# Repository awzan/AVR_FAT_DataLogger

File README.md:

# AVR_FAT_Data_Logger with DS18B20 temperature sensor

Files in this repository will work only on specific configuration of AVR Atmega32 microcontroller and its peripheries, described in Eagle file PM2016.sch (board scheme file)

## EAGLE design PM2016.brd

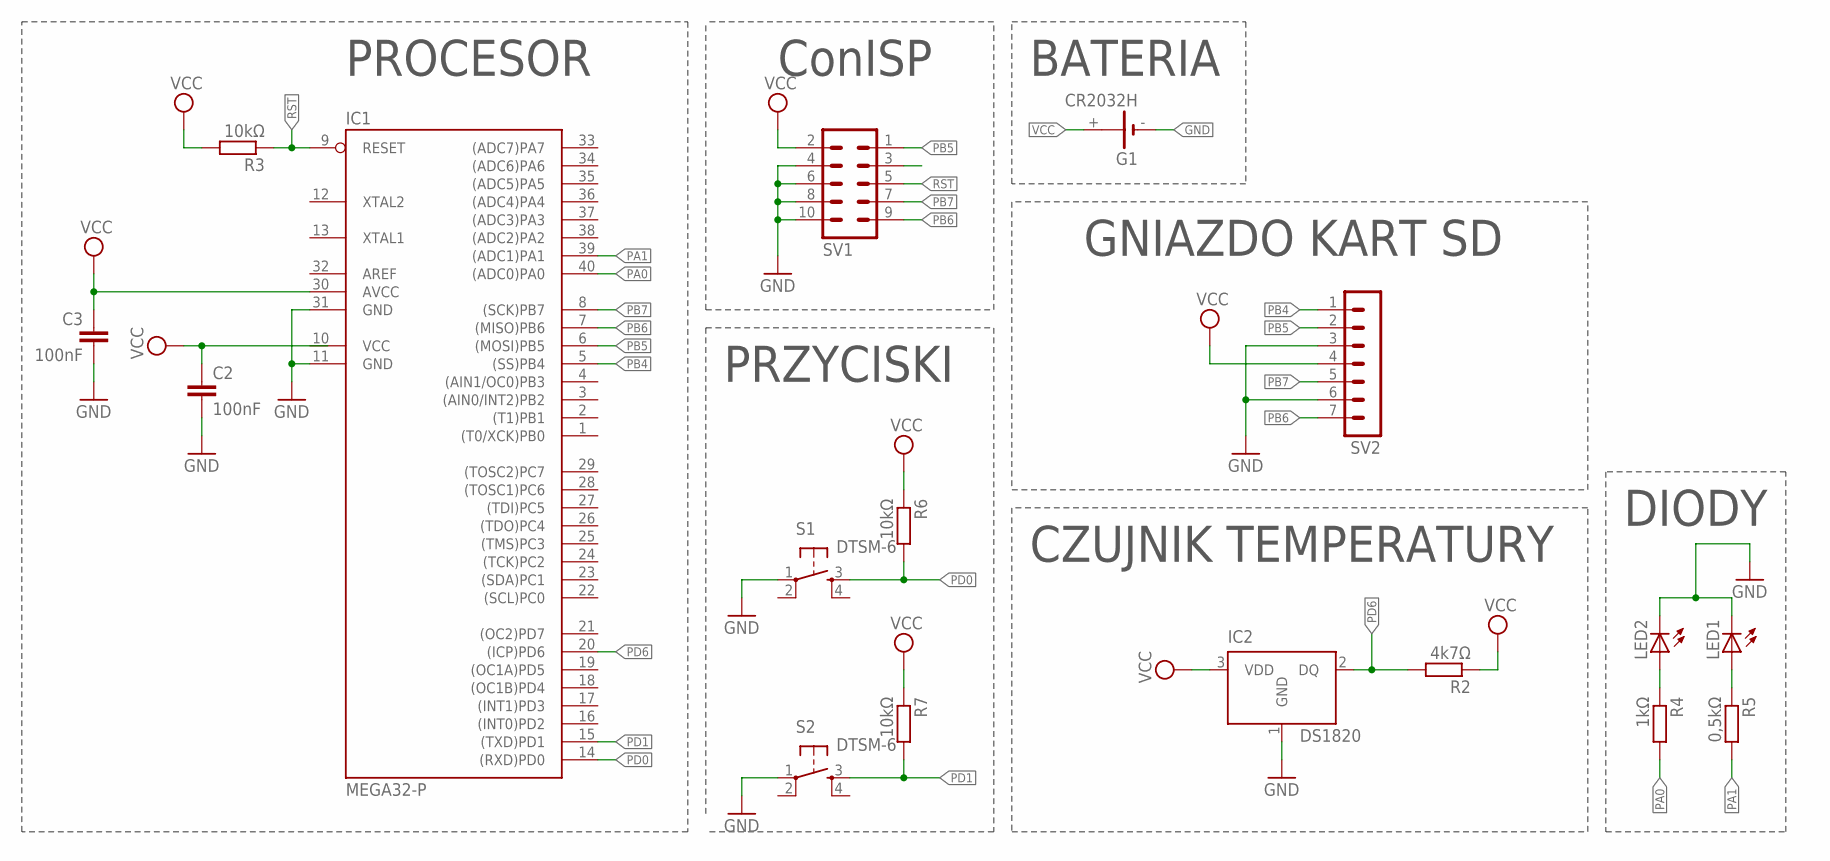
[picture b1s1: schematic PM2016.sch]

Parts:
C2, C3: 100nF; C050-025X075
G1: CR2032H
IC1: MEGA32-P; DIL40
IC2: DS1820; TO-92
LED1, LED2: LED5MM
R2: 4k7Ω; 0204/5
R3, R6, R7: 10kΩ; 0204/5
R4: 1kΩ; 0204/5
R5: 0,5kΩ; 0204/5
S1, S2: DTSM-6
SV1: ML10
SV2: MA07-1

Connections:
GND: C2.2, C3.2, G1.-, IC1.11 (GND), IC1.31 (GND), IC2.1 (GND), LED1.K (C), LED2.K (C), S1.1, S2.1, SV1.4, SV1.6, SV1.8, SV1.10, SV2.3, SV2.6
unnamed: LED2.A, R4.1
unnamed: LED1.A, R5.1
PA0: IC1.40 ((ADC0)PA0), R4.2
PA1: IC1.39 ((ADC1)PA1), R5.2
PB4: IC1.5 ((SS)PB4), SV2.1
PB5: IC1.6 ((MOSI)PB5), SV1.1, SV2.2
PB6: IC1.7 ((MISO)PB6), SV1.9, SV2.7
PB7: IC1.8 ((SCK)PB7), SV1.7, SV2.5
PD0: IC1.14 ((RXD)PD0), R6.2, S1.3
PD1: IC1.15 ((TXD)PD1), R7.2, S2.3
PD6: IC1.20 ((ICP)PD6), IC2.2 (DQ), R2.2
RST: IC1.9 (RESET), R3.1, SV1.5
VCC: C2.1, C3.1, G1.+, IC1.10 (VCC), IC1.30 (AVCC), IC2.3 (VDD), R2.1, R3.2, R6.1, R7.1, SV1.2, SV2.4

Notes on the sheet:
PROCESOR
BATERIA
DIODY
CZUJNIK TEMPERATURY
ConISP
GNIAZDO KART SD
PRZYCISKI

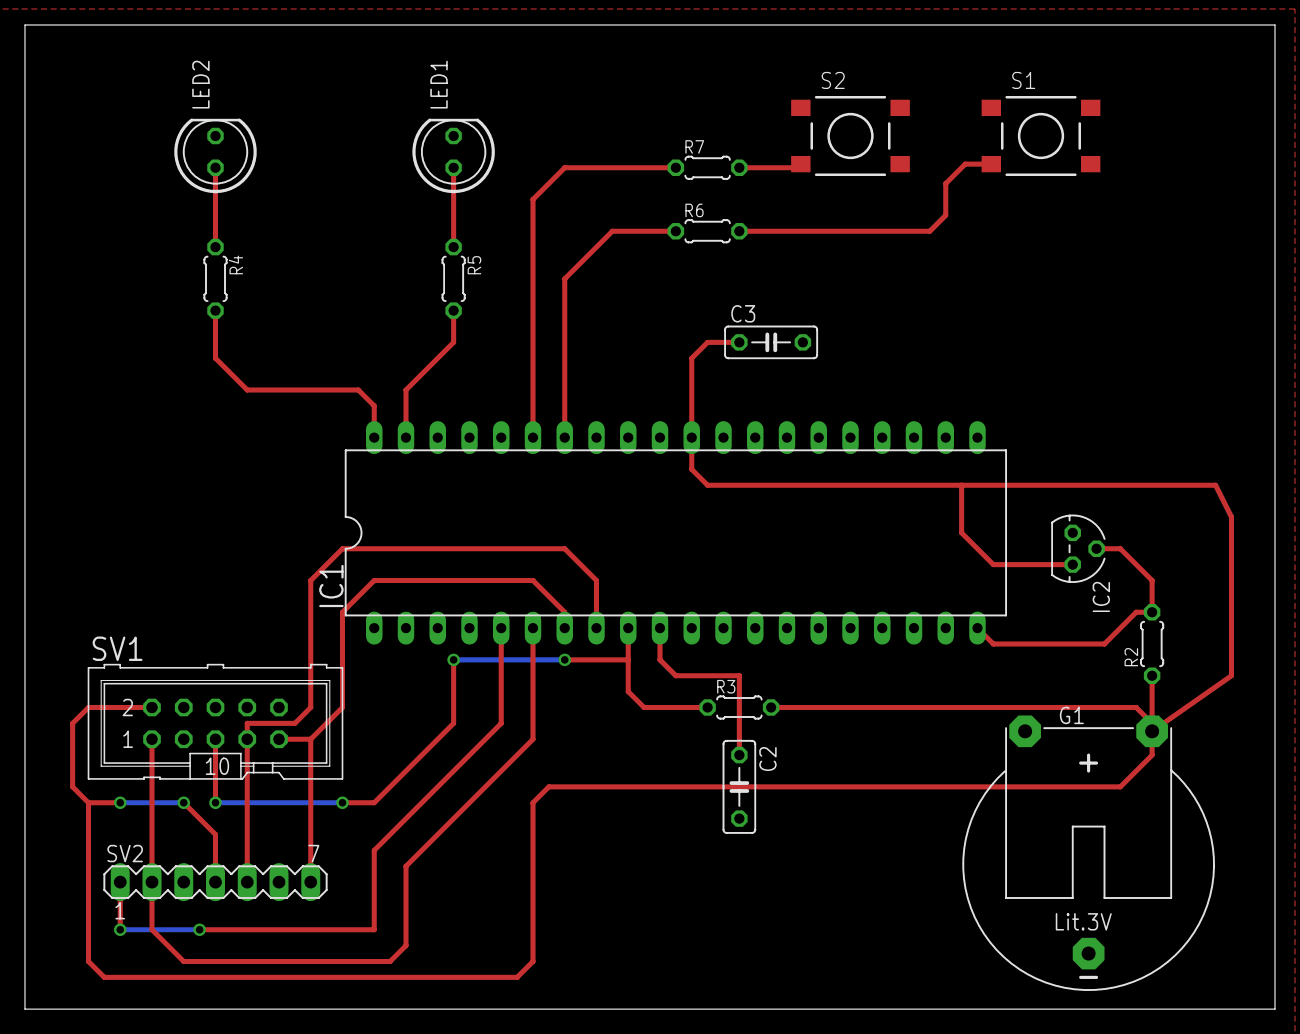
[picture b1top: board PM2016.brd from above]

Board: 2 copper layers, 100.0 x 78.7 mm, 17 parts (0 on the bottom side), 14 nets.

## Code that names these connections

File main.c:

/*----------------------------------------------------------------------*/
/* Temperature Data Logger on FATfs formatted SD cards */
/*----------------------------------------------------------------------*/


#include <avr/io.h>
#include <avr/pgmspace.h>
#include <avr/interrupt.h>
#include <util/delay.h>
#include <string.h>
#include "ff.h"
#include "diskio.h"
#include "rtc.h"
#include "ds18b20.h"
#include "ledy.h"
#include "przyciski.h"


#define SCK PB7
#define MOSI PB5
#define CS PB4
#define MISO PB6
static volatile int Stan = 0;

static volatile uint16_t hs = 0; //number of half seconds since the power up

void configure_timers()
{
  // 8 bit  TIMER0 configuration, normal mode

  TCCR0 = 1 << CS02 | 1<<CS00;// F_CPU / 1024 = 7812.5 Hz
  TIMSK |= 1 << TOIE0;// TIMER0_OVF Enable

  // 16 bit  TIMER1 configuration, CTC mode 

  TCCR1B |= (1 << CS12); // F_CPU / 256, assuming F_CPU = 8 000 000 hz, ~31 250 Hz
  TCCR1B |= (1 << WGM12); // CTC mode  
  OCR1A = 15624; // assuming F_CPU = 8 000 000 hz, interrupt every ~1/2sec
  TIMSK |= 1 << OCIE1A; // Timer/Counter1 Output Compare A Match Interrupt Enable.

  // 8 bit  TIMER2 configuration, CTC mode 

  TCCR2 |= WGM21; // CTC mode enable, compare to value set in OCR2
  TCCR2 = 1 << CS02 | 1<< CS01 | 1<<CS00;// F_CPU / 1024 = 7812.5 Hz
  OCR2 = 158-1;	// Timer2: 50Hz interval (OC2)
  // TCCR2 = 0b00001101;
  TIMSK |= 1<<OCIE2;	// Timer/Counter2 Output Compare Match Interrupt Enable

}

ISR( TIMER0_OVF_vect )
{ 

  if( czy_klawisz_wcisniety1() )
    Stan = 1;
  if( czy_klawisz_wcisniety2() && Stan == 1)
    Stan = 2;
}
ISR( TIMER1_COMPA_vect )
{
  hs++;
}

//DWORD acc_size;				/* Work register for fs command */
//WORD acc_files, acc_dirs;
FILINFO Finfo;
#if _USE_LFN
char Lfname[_MAX_LFN+1];
#endif


char Line[128];				/* Console input buffer */

FATFS Fatfs[_VOLUMES];		/* File system object for each logical drive */
BYTE Buff[256];			/* Working buffer */

volatile WORD Timer;		/* 100Hz increment timer */



#if _MULTI_PARTITION != 0
const PARTITION Drives[] = { {0,0}, {0,1} };
#endif



ISR(TIMER2_COMP_vect, ISR_NOBLOCK)
{
  Timer++;			/* Performance counter for this module */
  disk_timerproc();	/* Drive timer procedure of low level disk I/O module */
}



/*---------------------------------------------------------*/
/* User Provided Timer Function for FatFs module           */
/*---------------------------------------------------------*/
/* This is a real time clock service to be called from     */
/* FatFs module. Any valid time must be returned even if   */
/* the system does not support a real time clock.          */
/* This is not required in read-only configuration.        */


DWORD get_fattime ()
{
  RTC rtc;


  // Get local time 
  //rtc_gettime(&rtc);
  rtc.year = 2016;
  rtc.month = 7;
  rtc.mday = 10;
  rtc.hour = 16;
  rtc.min = 1;
  rtc.sec = 0;

  // Pack date and time into a DWORD variable 
  return	  ((DWORD)(rtc.year - 1980) << 25)
    | ((DWORD)rtc.month << 21)
    | ((DWORD)rtc.mday << 16)
    | ((DWORD)rtc.hour << 11)
    | ((DWORD)rtc.min << 5)
    | ((DWORD)rtc.sec >> 1);
}


void bufferFill(BYTE* buffer, char* napis, int dlugosc)
{
  int i;
  for(i = 0; i < 5-1; i++)
    buffer[i] = (BYTE)napis[i];
  buffer[5] = (BYTE)'\r';
  buffer[6] = (BYTE)'\n';
  //buffer[7] = (BYTE)'\0';
}

static void IoInit ()
{
  //PORTA = 0b11111111;	// Port A
  PORTB = 0b10110000; // Port B
  DDRB  = 0b11000000;
  // Configure pins for SPI 
  DDRB |= ((1<<CS) | (1<<MOSI) | (1<<SCK));
  PORTB |= (1<<CS); 
  PORTB |= (1<<MISO);
  SPCR |= ((1<<SPE) | (1<<MSTR)); // initialize hardware SPI support
  
  // Configure pins for LEDs

  DDRA |= ((1<<PA0) | (1<<PA1));
  //PORTC = 0b11111111;	// Port C

  // Configure pins for switches SW1 and SW2 <cto: 0 and 1>
  // Why is it pulled up to Vcc however?
  PORTD |= 1<<PD0 | 1 << PD1;
  //PORTD = 0b11111111; // Port D

  rtc_init();			// Initialize RTC

  sei();
}



/*-----------------------------------------------------------------------*/
/* Main                                                                  */


int main (void)
{
  IoInit();
  configure_timers();
  RED_LED_OFF;
  WHITE_LED_OFF;
  //char *ptr, *ptr2;
  long p1;
  //BYTE res, tryb, b1, *bp;
  BYTE tryb;
  //WORD w1;
  //UINT s1, s2;
  //DWORD ofs, sect = 0;
  //const BYTE ft[] = {0,12,16,32};
  //RTC rtc;
  //FATFS *fs;
  FIL file1;		// File object 
  //char* napis = "aaaaa";
  char  temp_str[10]; // String to put temperature in
  int dlugosc = 5; // Limit for buffer, probably unneeded
  int w;
  //double d;


#if _USE_LFN
  Finfo.lfname = Lfname;
  Finfo.lfsize = sizeof(Lfname);
#endif
  //blinkWhiteLEDnrazy(FR_OK);
  //d = ds18b20_gettemp()*100.0;
  //blinkWhiteLEDnrazy(FR_OK);
  w = (int) ds18b20_gettemp()*100.0;

  //blinkWhiteLEDnrazy(FR_OK);
  itoa(w,temp_str ,10);

  //blinkWhiteLEDnrazy(FR_OK);
  p1 = 0;
  //blinkWhiteLEDnrazy(FR_OK);
  tryb = 0b00001011;
  //blinkWhiteLEDnrazy(FR_OK);
  bufferFill(Buff, temp_str, dlugosc);
  //blinkWhiteLEDnrazy(FR_OK);
  /*DDRC &= ~(1<<PC2);
  //PORTC |= (1<<PC2);

  if(!(PINC & (1<<PC2)))
  blinkRedWhiteLED();

  blinkWhiteLED();*/
  blinkWhiteLEDnrazy(0);
  DSTATUS StatusKarty = disk_initialize((BYTE)p1) ;

  if( (StatusKarty & STA_NOINIT) == STA_NOINIT )
  {
    blinkRedLEDPaliKrotko();		
  }

  if( (StatusKarty & STA_PROTECT) == STA_PROTECT) // impossible to be true, sta_protect forced to low
  {
    blinkRedWhiteLED();		
  }
  if(f_mount((BYTE)p1, &Fatfs[p1]) != FR_OK)
    blinkRedLEDPaliDlugo();	


  if( (f_open(&file1, "T.txt", tryb) ) == FR_OK)
  {
    blinkRedLEDnrazy(0);
    while(1)
    {
      if(Stan == 1)
      {
        blinkRedLEDnrazy(0);

        //d = ds18b20_gettemp()*100.0;
        w = (int) ds18b20_gettemp()*100.0; // Fatfs library isn't able to deal with floats. Conv to int
        itoa(w,temp_str ,10);
        //itoa(ds/10,ds_str ,10);

        //if((f_write(&file1, Buff, dlugosc, &s2) & FR_OK) == FR_OK);
        //		blinkRedLEDnrazy(FR_OK);
        if((f_printf(&file1, "%4d",hs) != EOF ))
        {
          f_printf(&file1, " - ");
          //blinkWhiteLEDnrazy(FR_OK);
        }

        if((f_printf(&file1, temp_str) != EOF ))
        {
          f_printf(&file1, "\n");
          //blinkRedLEDnrazy(FR_OK);
        }

      }
      if(Stan == 2)
      {
        //blinkWhiteLEDnrazy(FR_OK);
        if((f_close(&file1) & FR_OK ) == FR_OK) 
          f_mount(0,0);
        blinkRedLEDPaliDlugo();
      }

    }
  }
  //if((f_mount(NULL, &Fatfs[p1]) & FR_OK == FR_OK))
  //blinkRedWhiteLED();

  return 0;
}

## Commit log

2016-07-28 Changes to be committed: new file: Makefile
2016-07-28 Changes to be committed: new file: diskio.h new file: ds18b20.c new file: ds18b20.h new file: ff.c new file: ff.h new file: ffconf.h new file: integer.h new file: ledy.c new file: ledy.h new file: ma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
